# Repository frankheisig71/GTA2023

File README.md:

# GTA2023
## Bewaesserung
Hier sind die Quelldateien für das Projekt Bewässerung

## webSteuerung
Hier sind die Quelldateien mit der eine Websteuerung realisiert werden kann

## Uebung (KiCad) 
### KiCad herunterladen
- [KiCad 6.0.11 für Windows x64](https://downloads.kicad.org/kicad/windows/explore/stable/download/kicad-6.0.11-x86_64.exe)

### Herunterladen des Projektes
- Klickt auf den grünen Button "<> Code" und wählt "Download Zip" 
  - das ist das einfachste, auch wenn dabei die Bilder und die README mitkommen - das könnt ihr dann weglöschen, ihr braucht nur den Ordner "Uebung"

### mit KiCad bearbeiten
- "File" -> "Open project"
- Mit dem Button  kommt man zum Schaltplan. Den könnt ihr Euch ansehen und vielleicht (später) versuchen etwas zu ändern
- Mit dem Button  kommt ihr zur Leiterplatte

### Leiterplatte

- die Leiterbahnen sind dort noch nicht verlegt - das könnt ihr mal probieren
  - benutzt das eingekreiste Symbol und klickt an ein Ende einer Verbindungslinie (Pfeil)
  - dann könnt ihr die Leiterbahn bis zum anderen Ende der Verbindungslinie verlegen
  - mit der "Esc" - Taste verlasst ihr den "Verlegemodus", mit "Strg" + "z" macht ihr die letzten Aktionen rückgängig
- unter "View" -> "3D - Viewer" könnt ihr Euch das Ergebnis anschauen

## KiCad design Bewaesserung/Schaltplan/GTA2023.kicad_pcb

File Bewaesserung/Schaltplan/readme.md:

# Schaltpläne und Leiterplatte
Mit KiCad erstellt

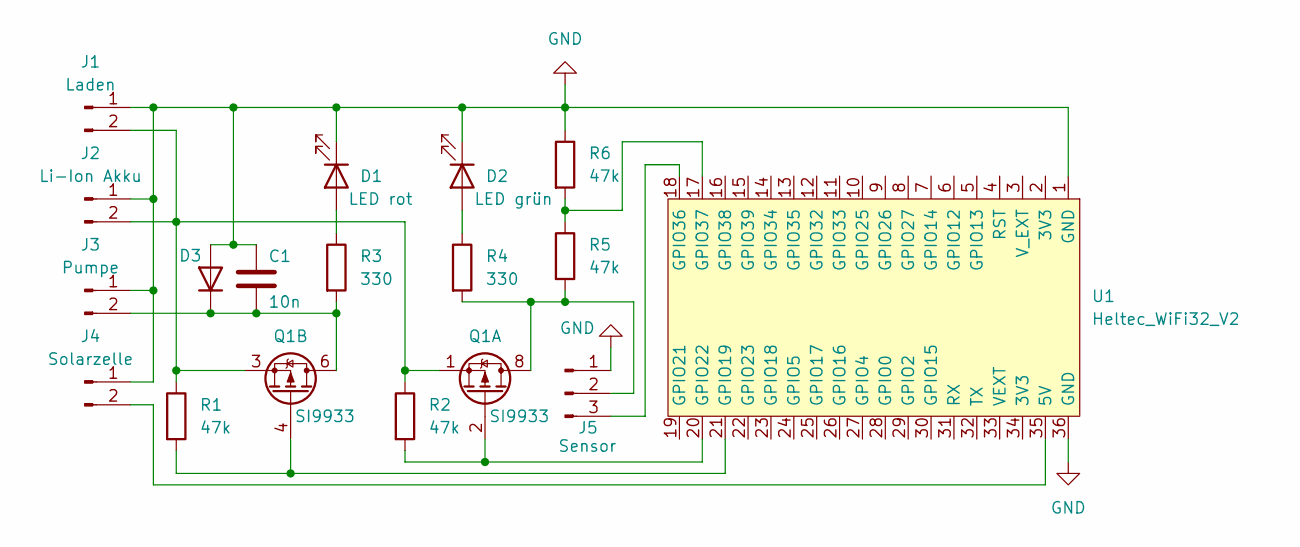
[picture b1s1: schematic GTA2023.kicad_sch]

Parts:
C1: 10n; C_Disc_D9.0mm_W5.0mm_P7.50mm
D1: LED rot; LED_D5.0mm
D2: LED grün; LED_D5.0mm
D3: D_A-405_P7.62mm_Horizontal
J1: Laden; PinHeader_1x02_P2.54mm_Vertical
J2: Li-Ion Akku; PinHeader_1x02_P2.54mm_Vertical
J3: Pumpe; PinHeader_1x02_P2.54mm_Vertical
J4: Solarzelle; PinHeader_1x02_P2.54mm_Vertical
J5: Sensor; PinHeader_1x03_P2.54mm_Vertical
Q1: SI9933; SOIC-8_3.9x4.9mm_P1.27mm
R1, R2, R5, R6: 47k; R_Axial_DIN0207_L6.3mm_D2.5mm_P10.16mm_Horizontal
R3, R4: 330; R_Axial_DIN0207_L6.3mm_D2.5mm_P10.16mm_Horizontal
U1: Heltec_WiFi32_V2; HeltecWifi32

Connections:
GND: C1.1, D1.1 (K), D2.1 (K), D3.2 (A), J1.1, J2.1, J3.1, J4.1, J5.1, R6.1, U1.1 (GND), U1.36 (GND)
unnamed: C1.2, D3.1 (K), J3.2, Q1.5 (D2), Q1.6 (D2), R3.2
unnamed: D1.2 (A), R3.1
unnamed: D2.2 (A), R4.1
unnamed: J1.2, J2.2, Q1.1 (S1), Q1.3 (S2), R1.1, R2.1
unnamed: J4.2, U1.35 (5V)
unnamed: J5.2, Q1.7 (D1), Q1.8 (D1), R4.2, R5.2
unnamed: J5.3, U1.18 (GPIO36)
unnamed: Q1.2 (G1), R2.2, U1.20 (GPIO22)
unnamed: Q1.4 (G2), R1.2, U1.21 (GPIO19)
unnamed: R5.1, R6.2, U1.17 (GPIO37)

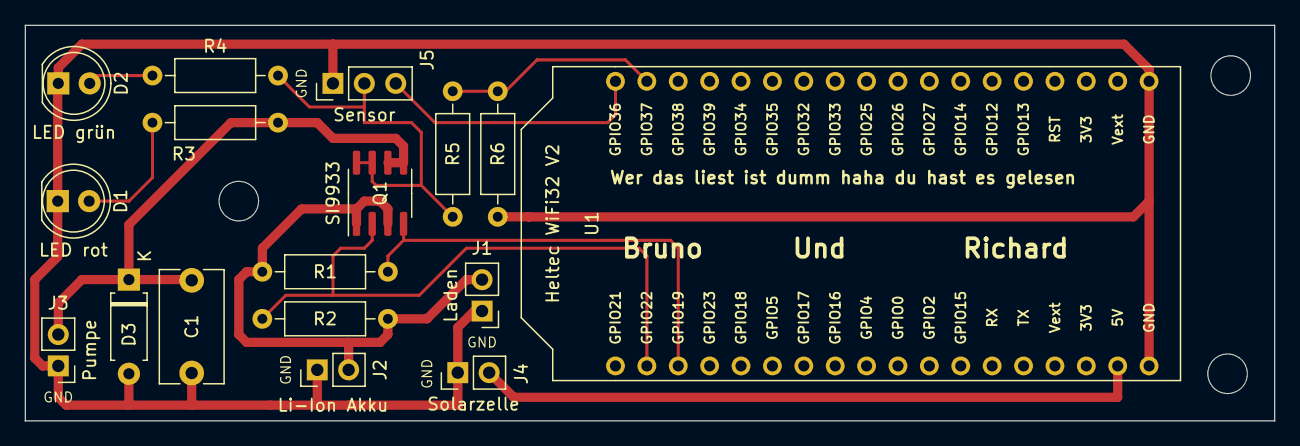
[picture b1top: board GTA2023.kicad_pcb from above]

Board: 2 copper layers, 101.1 x 32.0 mm, 20 parts (0 on the bottom side), 11 nets.

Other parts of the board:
 : MountingHole_3.2mm_M3
 #2,  #3: MountingHole_3.2mm_M3

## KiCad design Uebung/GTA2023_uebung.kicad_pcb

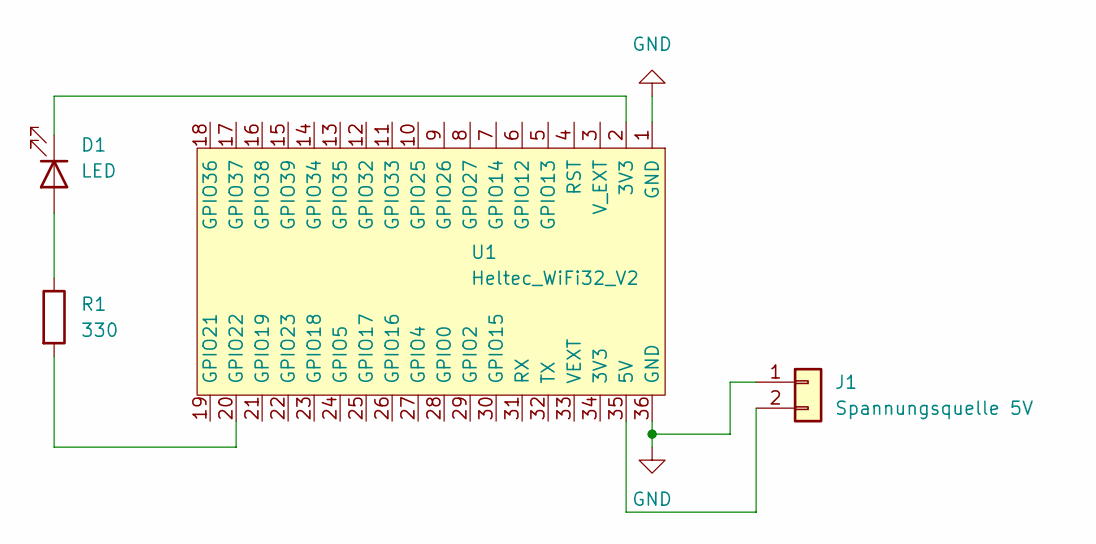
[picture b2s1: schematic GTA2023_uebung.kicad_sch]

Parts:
D1: LED; LED_D5.0mm
J1: Spannungsquelle 5V; PinSocket_1x02_P2.54mm_Vertical
R1: 330; R_Axial_DIN0207_L6.3mm_D2.5mm_P10.16mm_Horizontal
U1: Heltec_WiFi32_V2; HeltecWifi32

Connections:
GND: J1.1, U1.1 (GND), U1.36 (GND)
unnamed: D1.2 (A), R1.1
unnamed: D1.1 (K), U1.2 (3V3)
unnamed: R1.2, U1.20 (GPIO22)
unnamed: J1.2, U1.35 (5V)

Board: 2 copper layers, 4 parts (0 on the bottom side), 5 nets, no tracks yet.

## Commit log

2023-05-09 add exercise
2023-05-09 add pictures
2023-05-09 Korrektur
